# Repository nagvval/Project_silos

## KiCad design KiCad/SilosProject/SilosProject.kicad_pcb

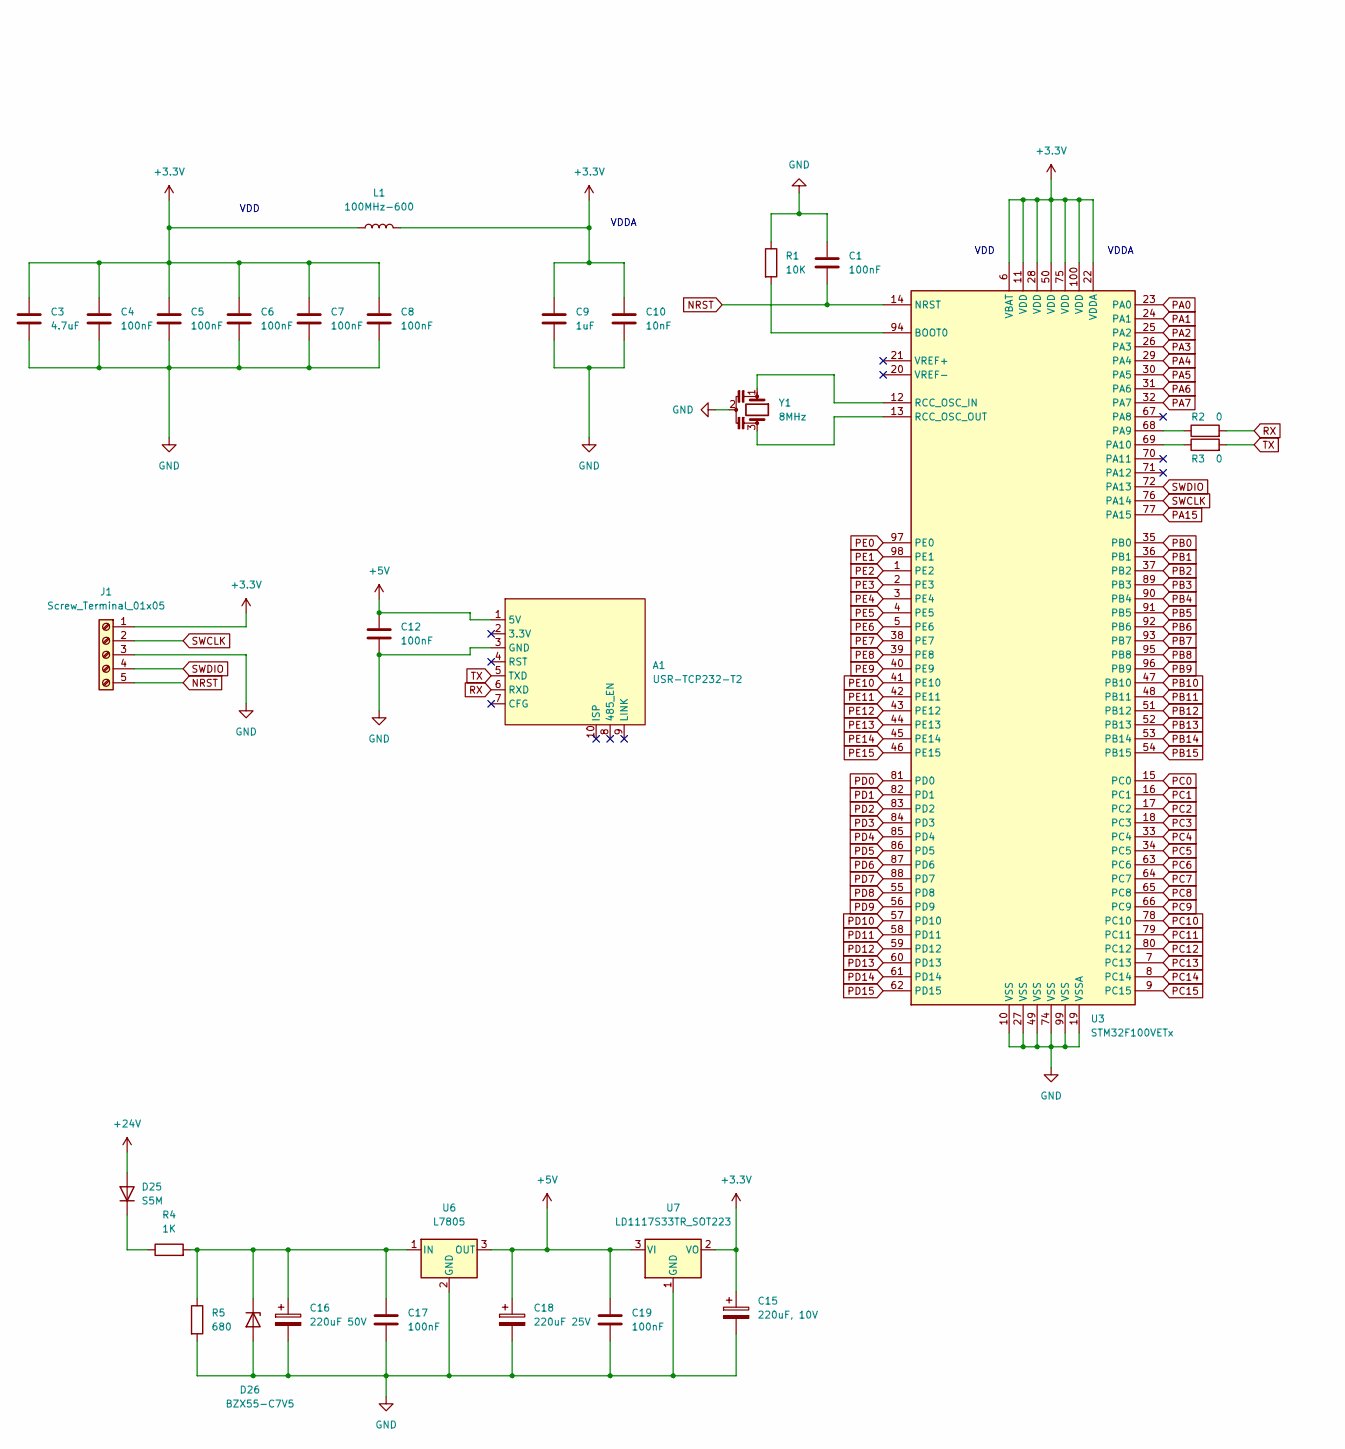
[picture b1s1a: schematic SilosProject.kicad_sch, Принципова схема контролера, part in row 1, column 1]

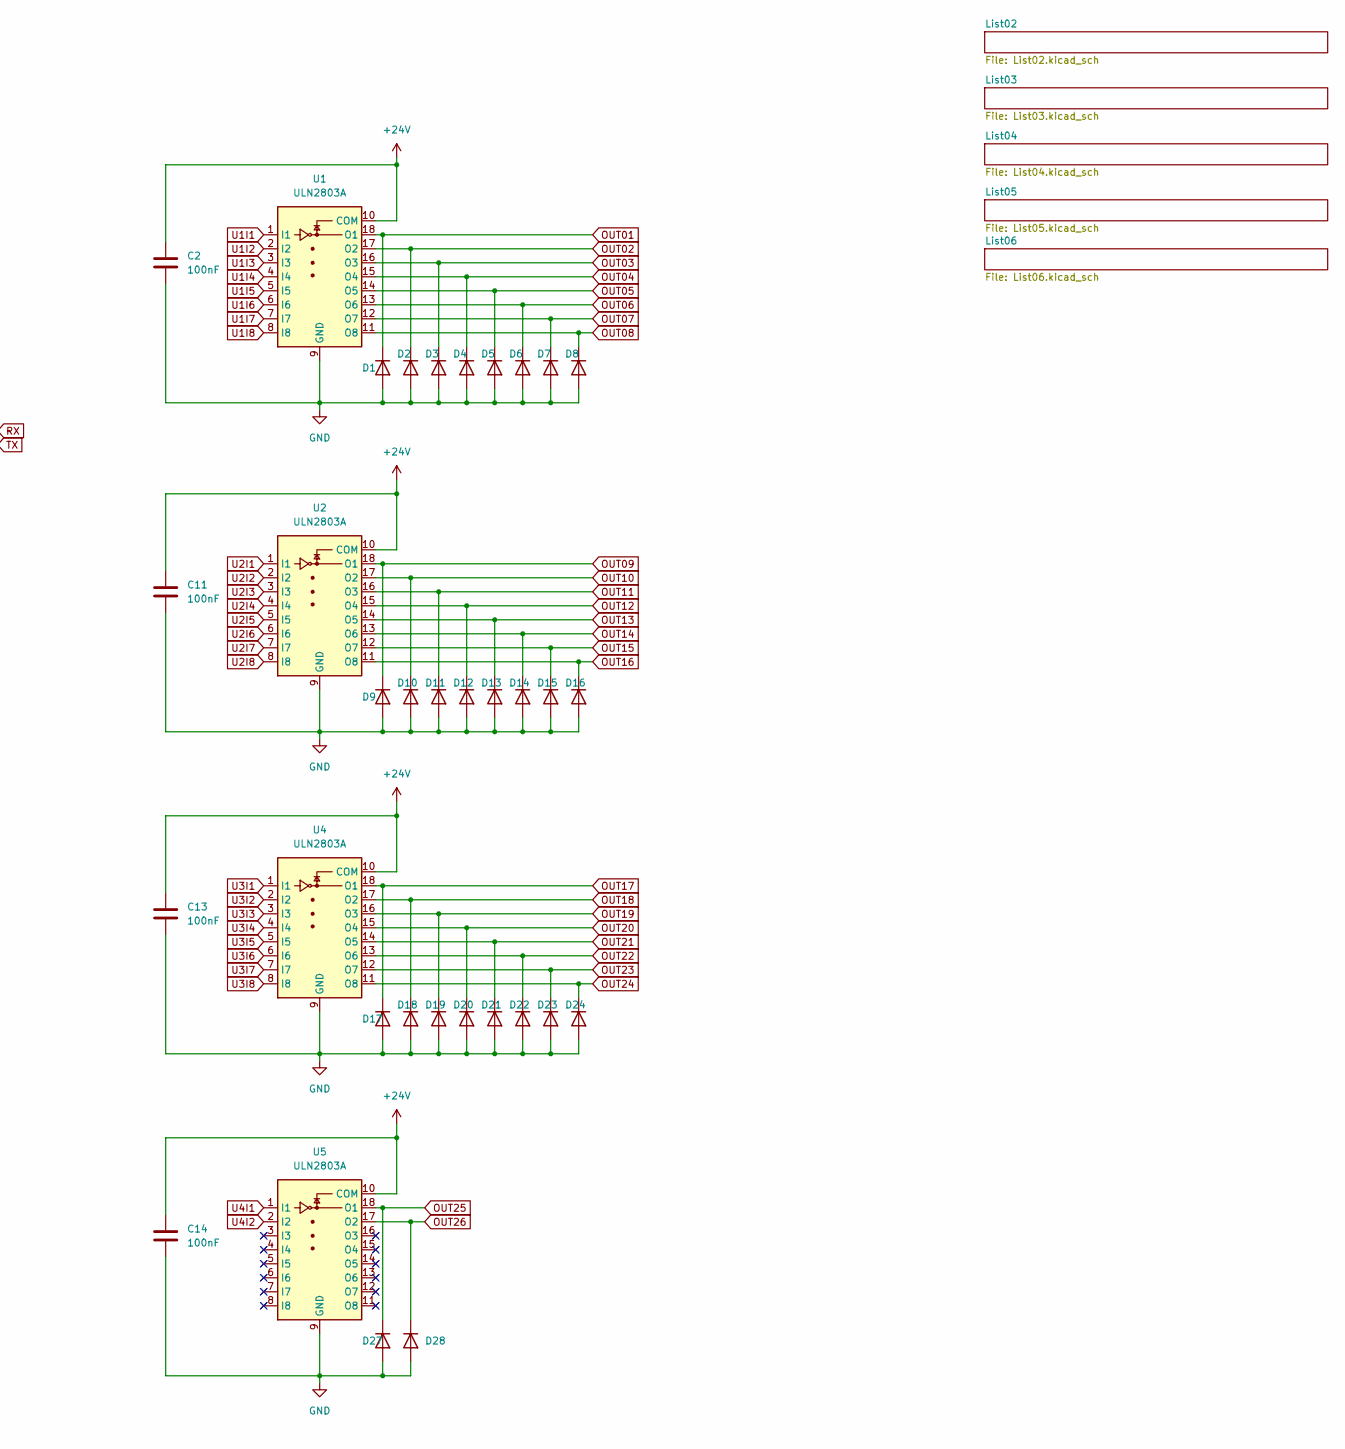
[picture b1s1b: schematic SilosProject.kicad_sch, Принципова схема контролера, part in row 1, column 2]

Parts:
A1: USR-TCP232-T2; USR-TCP232-T2_MODUL
C1, C2, C4, C5, C6, C7, C8, C11, C12, C13, C14, C17, C19: 100nF; C_0805_2012Metric
C3: 4.7uF; C_0805_2012Metric
C9: 1uF; C_0805_2012Metric
C10: 10nF; C_0805_2012Metric
C15: 220uF, 10V; C_Radial_D6.3mm_H11.0mm_P2.50mm
C16: 220uF 50V; C_Radial_D10.0mm_H12.5mm_P5.00mm
C18: 220uF 25V; C_Radial_D6.3mm_H11.0mm_P2.50mm
D1, D2, D3, D4, D5, D6, D7, D8, D9, D10, D11, D12, D13, D14, D15, D16, D17, D18, D19, D20, D21, D22, D23, D24, D27, D28: 1N4007; D_DO-41_SOD81_P10.16mm_Horizontal
D25: S5M; D_SMC
D26: BZX55-C7V5; D_SOD-123
J1: Screw_Terminal_01x05; PinHeader_1x05_P2.54mm_Vertical
L1: 100MHz-600; L_0805_2012Metric_Pad1.05x1.20mm_HandSolder
R1: 10K; C_0805_2012Metric
R2, R3: 0; R_0805_2012Metric
R4: 1K; R_2512_6332Metric
R5: 680; R_2512_6332Metric
U1, U2, U4, U5: ULN2803A; SOIC-18W_7.5x11.6mm_P1.27mm
U3: STM32F100VETx; LQFP-100_14x14mm_P0.5mm
U6: L7805; TO-220-3_Vertical
U7: LD1117S33TR_SOT223; SOT-223-3_TabPin2
Y1: 8MHz; Resonator_SMD_Murata_CSTxExxV-3Pin_3.0x1.1mm

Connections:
+3.3V: C3.1, C4.1, C5.1, C6.1, C7.1, C8.1, C9.1, C10.1, C15.1, J1.1, L1.1, L1.2, U3.6 (VBAT), U3.11 (VDD), U3.22 (VDDA), U3.28 (VDD), U3.50 (VDD), U3.75 (VDD), U3.100 (VDD), U7.2 (VO); also elsewhere on the board
+5V: A1.1 (5V), C12.1, C18.1, C19.1, U6.3 (OUT), U7.3 (VI); also elsewhere on the board
+24V: C2.1, C11.1, C13.1, C14.1, D25.2 (A), U1.10 (COM), U2.10 (COM), U4.10 (COM), U5.10 (COM); also elsewhere on the board
GND: A1.3 (GND), C1.2, C2.2, C3.2, C4.2, C5.2, C6.2, C7.2, C8.2, C9.2, C10.2, C11.2, C12.2, C13.2, C14.2, C15.2, C16.2, C17.2, C18.2, C19.2, D1.2 (A), D2.2 (A), D3.2 (A), D4.2 (A), D5.2 (A), D6.2 (A), D7.2 (A), D8.2 (A), D9.2 (A), D10.2 (A), D11.2 (A), D12.2 (A), D13.2 (A), D14.2 (A), D15.2 (A), D16.2 (A), D17.2 (A), D18.2 (A), D19.2 (A), D20.2 (A), D21.2 (A), D22.2 (A), D23.2 (A), D24.2 (A), D26.2 (A), D27.2 (A), D28.2 (A), J1.3, R1.1, R5.2, U1.9 (GND), U2.9 (GND), U3.10 (VSS), U3.19 (VSSA), U3.27 (VSS), U3.49 (VSS), U3.74 (VSS), U3.99 (VSS), U4.9 (GND), U5.9 (GND), U6.2 (GND), U7.1 (GND), Y1.2; also elsewhere on the board
NRST: C1.1, J1.5, U3.14 (NRST)
unnamed: C16.1, C17.1, D26.1 (K), R4.2, R5.1, U6.1 (IN)
unnamed: D25.1 (K), R4.1
unnamed: R1.2, U3.94 (BOOT0)
unnamed: R2.1, U3.68 (PA9)
unnamed: R3.1, U3.69 (PA10)
unnamed: U3.12 (RCC_OSC_IN), Y1.1
unnamed: U3.13 (RCC_OSC_OUT), Y1.3
OUT01: D1.1 (K), U1.18 (O1); also elsewhere on the board
OUT02: D2.1 (K), U1.17 (O2); also elsewhere on the board
OUT03: D3.1 (K), U1.16 (O3); also elsewhere on the board
OUT04: D4.1 (K), U1.15 (O4); also elsewhere on the board
OUT05: D5.1 (K), U1.14 (O5); also elsewhere on the board
OUT06: D6.1 (K), U1.13 (O6); also elsewhere on the board
OUT07: D7.1 (K), U1.12 (O7); also elsewhere on the board
OUT08: D8.1 (K), U1.11 (O8); also elsewhere on the board
OUT09: D9.1 (K), U2.18 (O1); also elsewhere on the board
OUT10: D10.1 (K), U2.17 (O2); also elsewhere on the board
OUT11: D11.1 (K), U2.16 (O3); also elsewhere on the board
OUT12: D12.1 (K), U2.15 (O4); also elsewhere on the board
OUT13: D13.1 (K), U2.14 (O5); also elsewhere on the board
OUT14: D14.1 (K), U2.13 (O6); also elsewhere on the board
OUT15: D15.1 (K), U2.12 (O7); also elsewhere on the board
OUT16: D16.1 (K), U2.11 (O8); also elsewhere on the board
OUT17: D17.1 (K), U4.18 (O1); also elsewhere on the board
OUT18: D18.1 (K), U4.17 (O2); also elsewhere on the board
OUT19: D19.1 (K), U4.16 (O3); also elsewhere on the board
OUT20: D20.1 (K), U4.15 (O4); also elsewhere on the board
OUT21: D21.1 (K), U4.14 (O5); also elsewhere on the board
OUT22: D22.1 (K), U4.13 (O6); also elsewhere on the board
OUT23: D23.1 (K), U4.12 (O7); also elsewhere on the board
OUT24: D24.1 (K), U4.11 (O8); also elsewhere on the board
OUT25: D27.1 (K), U5.18 (O1); also elsewhere on the board
OUT26: D28.1 (K), U5.17 (O2); also elsewhere on the board
PA0: U3.23 (PA0); also elsewhere on the board
PA1: U3.24 (PA1); also elsewhere on the board
PA2: U3.25 (PA2); also elsewhere on the board
PA3: U3.26 (PA3); also elsewhere on the board
PA4: U3.29 (PA4); also elsewhere on the board
PA5: U3.30 (PA5); also elsewhere on the board
PA6: U3.31 (PA6); also elsewhere on the board
PA7: U3.32 (PA7); also elsewhere on the board
PA15: U3.77 (PA15); also elsewhere on the board
PB0: U3.35 (PB0); also elsewhere on the board
PB1: U3.36 (PB1); also elsewhere on the board
PB2: U3.37 (PB2); also elsewhere on the board
PB3: U3.89 (PB3); also elsewhere on the board
PB4: U3.90 (PB4); also elsewhere on the board
PB5: U3.91 (PB5); also elsewhere on the board
PB6: U3.92 (PB6); also elsewhere on the board
PB7: U3.93 (PB7); also elsewhere on the board
PB8: U3.95 (PB8); also elsewhere on the board
PB9: U3.96 (PB9); also elsewhere on the board
PB10: U3.47 (PB10); also elsewhere on the board
PB11: U3.48 (PB11); also elsewhere on the board
PB12: U3.51 (PB12); also elsewhere on the board
PB13: U3.52 (PB13); also elsewhere on the board
PB14: U3.53 (PB14); also elsewhere on the board
PB15: U3.54 (PB15); also elsewhere on the board
PC0: U3.15 (PC0); also elsewhere on the board
PC1: U3.16 (PC1); also elsewhere on the board
PC2: U3.17 (PC2); also elsewhere on the board
PC3: U3.18 (PC3); also elsewhere on the board
PC4: U3.33 (PC4); also elsewhere on the board
PC5: U3.34 (PC5); also elsewhere on the board
PC6: U3.63 (PC6); also elsewhere on the board
PC7: U3.64 (PC7); also elsewhere on the board
PC8: U3.65 (PC8); also elsewhere on the board
PC9: U3.66 (PC9); also elsewhere on the board
PC10: U3.78 (PC10); also elsewhere on the board
PC11: U3.79 (PC11); also elsewhere on the board
PC12: U3.80 (PC12); also elsewhere on the board
PC13: U3.7 (PC13); also elsewhere on the board
PC14: U3.8 (PC14); also elsewhere on the board
PC15: U3.9 (PC15); also elsewhere on the board
PD0: U3.81 (PD0); also elsewhere on the board
PD1: U3.82 (PD1); also elsewhere on the board
PD2: U3.83 (PD2); also elsewhere on the board
PD3: U3.84 (PD3); also elsewhere on the board
PD4: U3.85 (PD4); also elsewhere on the board
PD5: U3.86 (PD5); also elsewhere on the board
PD6: U3.87 (PD6); also elsewhere on the board
PD7: U3.88 (PD7); also elsewhere on the board
PD8: U3.55 (PD8); also elsewhere on the board
PD9: U3.56 (PD9); also elsewhere on the board
PD10: U3.57 (PD10); also elsewhere on the board
PD11: U3.58 (PD11); also elsewhere on the board
PD12: U3.59 (PD12); also elsewhere on the board
PD13: U3.60 (PD13); also elsewhere on the board
PD14: U3.61 (PD14); also elsewhere on the board
PD15: U3.62 (PD15); also elsewhere on the board
PE0: U3.97 (PE0); also elsewhere on the board
PE1: U3.98 (PE1); also elsewhere on the board
PE2: U3.1 (PE2); also elsewhere on the board
PE3: U3.2 (PE3); also elsewhere on the board
PE4: U3.3 (PE4); also elsewhere on the board
PE5: U3.4 (PE5); also elsewhere on the board
PE6: U3.5 (PE6); also elsewhere on the board
PE7: U3.38 (PE7); also elsewhere on the board
PE8: U3.39 (PE8); also elsewhere on the board
PE9: U3.40 (PE9); also elsewhere on the board
PE10: U3.41 (PE10); also elsewhere on the board
PE11: U3.42 (PE11); also elsewhere on the board
PE12: U3.43 (PE12); also elsewhere on the board
PE13: U3.44 (PE13); also elsewhere on the board
PE14: U3.45 (PE14); also elsewhere on the board
PE15: U3.46 (PE15); also elsewhere on the board
RX: A1.6 (RXD), R2.2
SWCLK: J1.2, U3.76 (PA14)
SWDIO: J1.4, U3.72 (PA13)
TX: A1.5 (TXD), R3.2
U1I1: U1.1 (I1); also elsewhere on the board
U1I2: U1.2 (I2); also elsewhere on the board
U1I3: U1.3 (I3); also elsewhere on the board
U1I4: U1.4 (I4); also elsewhere on the board
U1I5: U1.5 (I5); also elsewhere on the board
U1I6: U1.6 (I6); also elsewhere on the board
U1I7: U1.7 (I7); also elsewhere on the board
U1I8: U1.8 (I8); also elsewhere on the board
U2I1: U2.1 (I1); also elsewhere on the board
U2I2: U2.2 (I2); also elsewhere on the board
U2I3: U2.3 (I3); also elsewhere on the board
U2I4: U2.4 (I4); also elsewhere on the board
U2I5: U2.5 (I5); also elsewhere on the board
U2I6: U2.6 (I6); also elsewhere on the board
U2I7: U2.7 (I7); also elsewhere on the board
U2I8: U2.8 (I8); also elsewhere on the board
U3I1: U4.1 (I1); also elsewhere on the board
U3I2: U4.2 (I2); also elsewhere on the board
U3I3: U4.3 (I3); also elsewhere on the board
U3I4: U4.4 (I4); also elsewhere on the board
U3I5: U4.5 (I5); also elsewhere on the board
U3I6: U4.6 (I6); also elsewhere on the board
U3I7: U4.7 (I7); also elsewhere on the board
U3I8: U4.8 (I8); also elsewhere on the board
U4I1: U5.1 (I1); also elsewhere on the board
U4I2: U5.2 (I2); also elsewhere on the board

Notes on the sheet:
VDD
VDDA

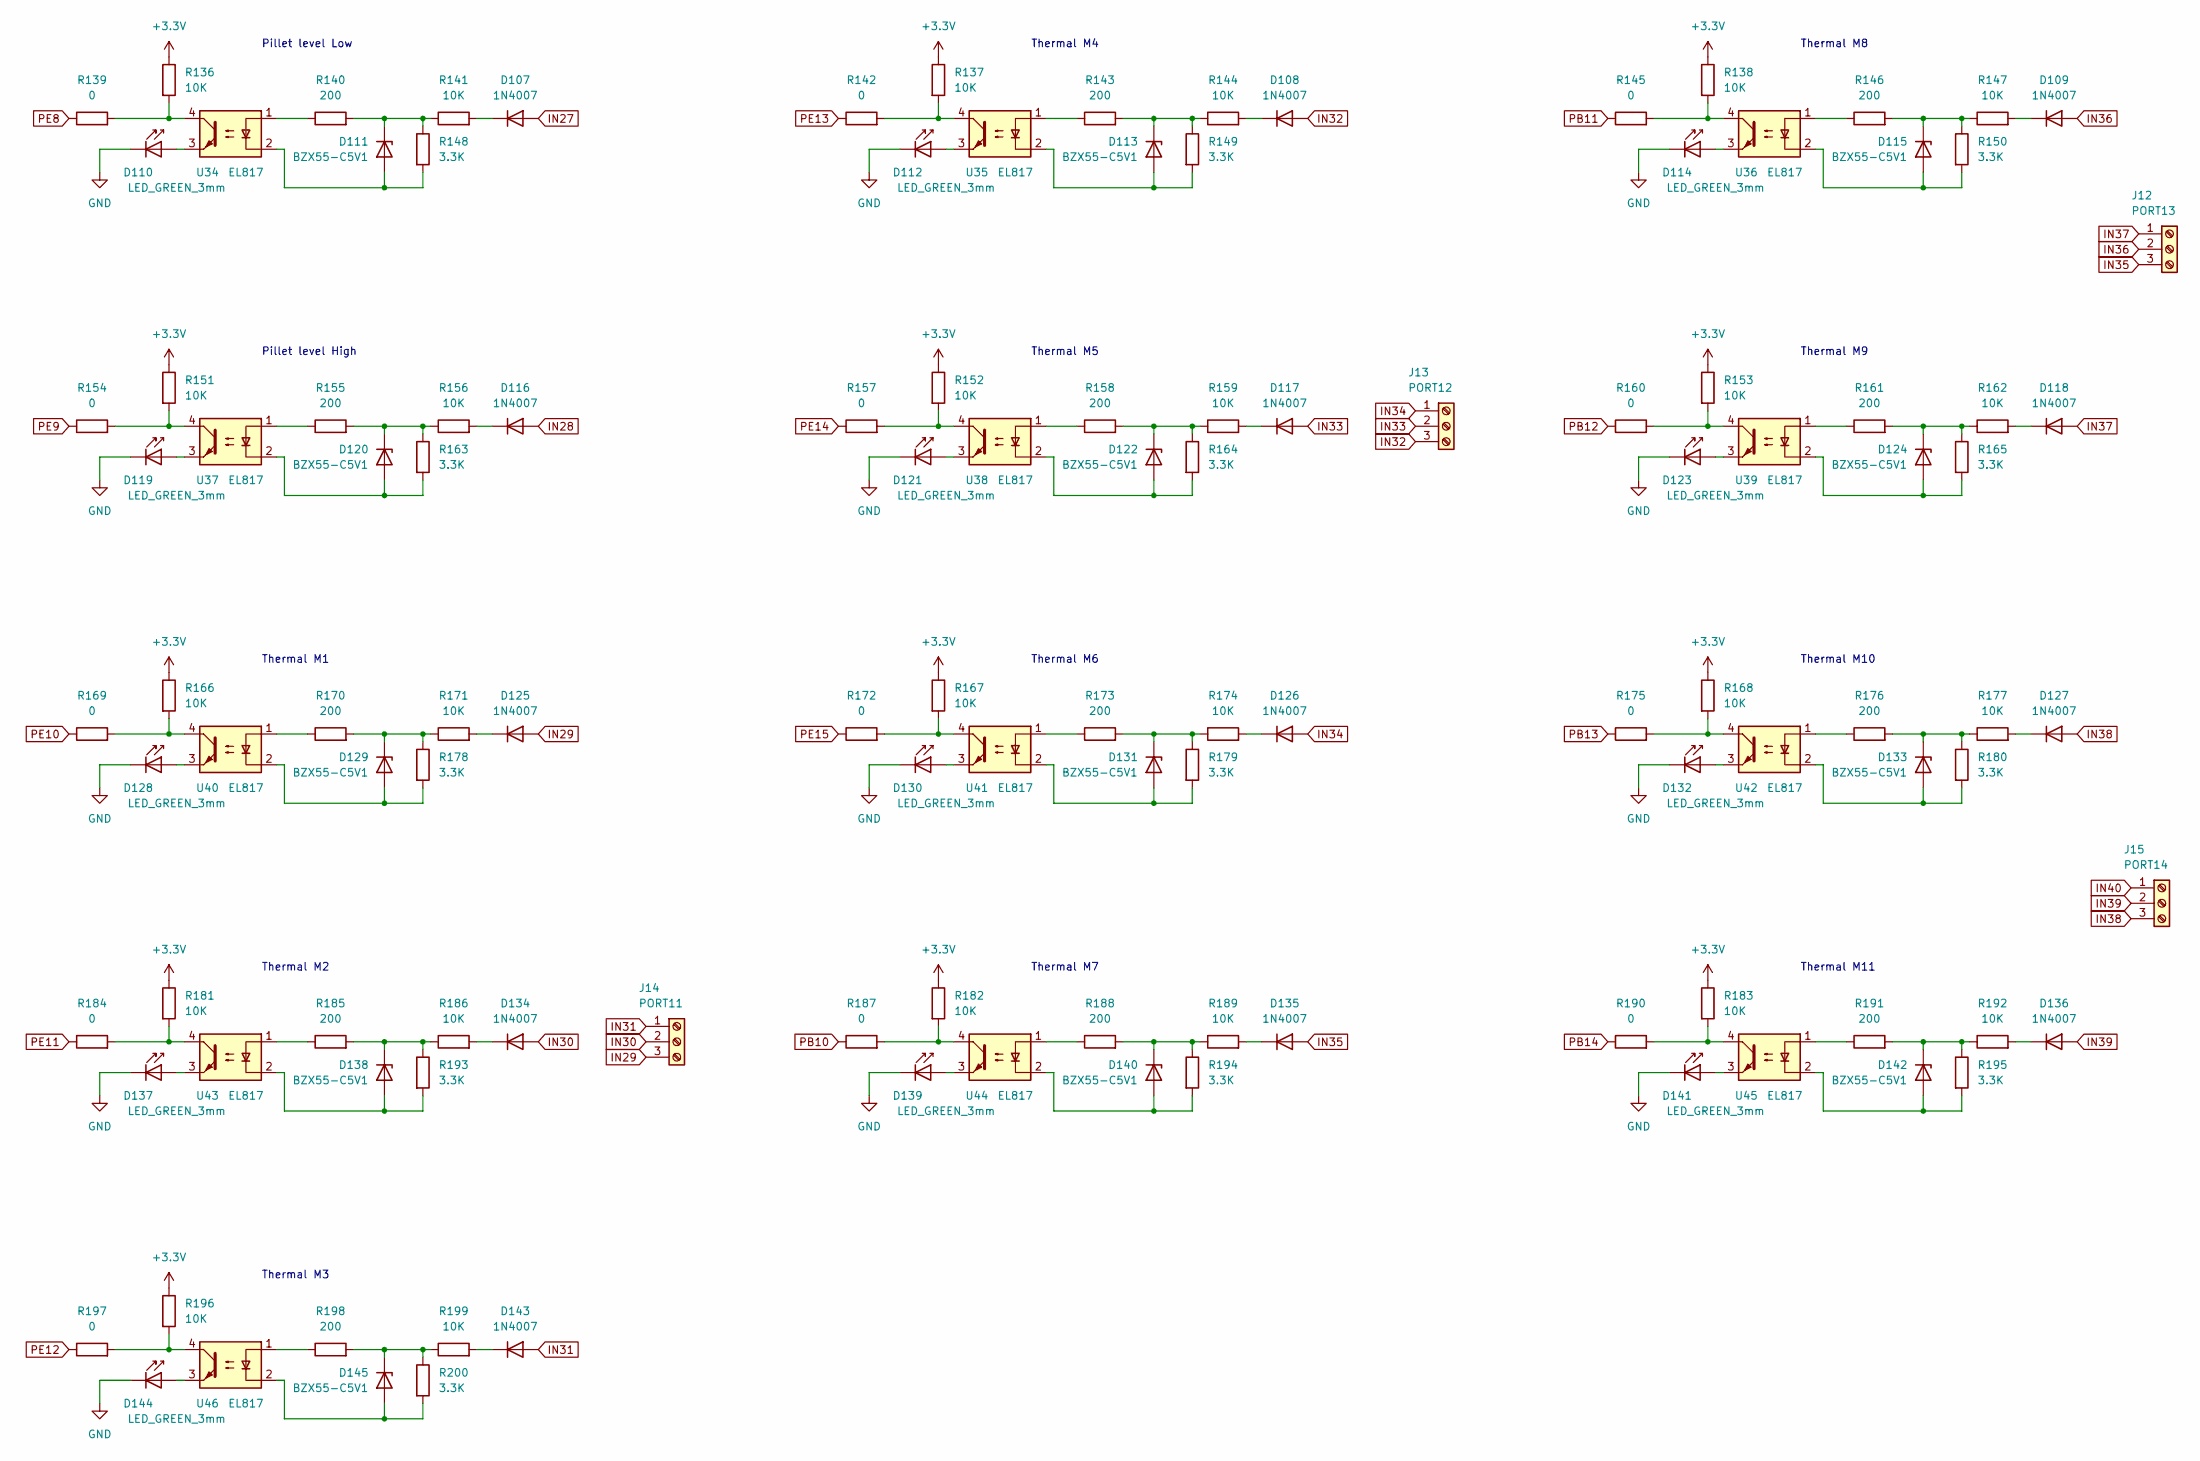
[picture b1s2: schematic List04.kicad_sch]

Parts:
D107, D108, D109, D116, D117, D118, D125, D126, D127, D134, D135, D136, D143: 1N4007; D_DO-41_SOD81_P10.16mm_Horizontal
D110, D112, D114, D119, D121, D123, D128, D130, D132, D137, D139, D141, D144: LED_GREEN_3mm; LED_D3.0mm
D111, D113, D115, D120, D122, D124, D129, D131, D133, D138, D140, D142, D145: BZX55-C5V1; D_DO-35_SOD27_P2.54mm_Vertical_AnodeUp
J12: PORT13; DG306-5.0-03P-12-00A
J13: PORT12; DG306-5.0-03P-12-00A
J14: PORT11; DG306-5.0-03P-12-00A
J15: PORT14; DG306-5.0-03P-12-00A
R136, R137, R138, R151, R152, R153, R166, R167, R168, R181, R182, R183, R196: 10K; R_0805_2012Metric
R139, R142, R145, R154, R157, R160, R169, R172, R175, R184, R187, R190, R197: 0; R_0805_2012Metric
R140, R143, R146, R155, R158, R161, R170, R173, R176, R185, R188, R191, R198: 200; R_0805_2012Metric
R141, R144, R147, R156, R159, R162, R171, R174, R177, R186, R189, R192, R199: 10K; R_2512_6332Metric
R148, R149, R150, R163, R164, R165, R178, R179, R180, R193, R194, R195, R200: 3.3K; R_1206_3216Metric
U34, U35, U36, U37, U38, U39, U40, U41, U42, U43, U44, U45, U46: EL817; DIP-4_W7.62mm

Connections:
+3.3V: R136.1, R137.1, R138.1, R151.1, R152.1, R153.1, R166.1, R167.1, R168.1, R181.1, R182.1, R183.1, R196.1; also elsewhere on the board
GND: D110.1 (K), D112.1 (K), D114.1 (K), D119.1 (K), D121.1 (K), D123.1 (K), D128.1 (K), D130.1 (K), D132.1 (K), D137.1 (K), D139.1 (K), D141.1 (K), D144.1 (K); also elsewhere on the board
IN27: D107.2 (A); also elsewhere on the board
IN28: D116.2 (A); also elsewhere on the board
IN29: D125.2 (A), J14.3
IN30: D134.2 (A), J14.2
IN31: D143.2 (A), J14.1
IN32: D108.2 (A), J13.3
IN33: D117.2 (A), J13.2
IN34: D126.2 (A), J13.1
IN35: D135.2 (A), J12.3
IN36: D109.2 (A), J12.2
IN37: D118.2 (A), J12.1
IN38: D127.2 (A), J15.3
IN39: D136.2 (A), J15.2
IN40: J15.1; also elsewhere on the board
unnamed: D107.1 (K), R141.2
unnamed: D108.1 (K), R144.2
unnamed: D109.1 (K), R147.2
unnamed: D110.2 (A), U34.3
unnamed: D111.1 (K), R140.2, R141.1, R148.1
unnamed: D111.2 (A), R148.2, U34.2
unnamed: D112.2 (A), U35.3
unnamed: D113.1 (K), R143.2, R144.1, R149.1
unnamed: D113.2 (A), R149.2, U35.2
unnamed: D114.2 (A), U36.3
unnamed: D115.1 (K), R146.2, R147.1, R150.1
unnamed: D115.2 (A), R150.2, U36.2
unnamed: D116.1 (K), R156.2
unnamed: D117.1 (K), R159.2
unnamed: D118.1 (K), R162.2
unnamed: D119.2 (A), U37.3
unnamed: D120.1 (K), R155.2, R156.1, R163.1
unnamed: D120.2 (A), R163.2, U37.2
unnamed: D121.2 (A), U38.3
unnamed: D122.1 (K), R158.2, R159.1, R164.1
unnamed: D122.2 (A), R164.2, U38.2
unnamed: D123.2 (A), U39.3
unnamed: D124.1 (K), R161.2, R162.1, R165.1
unnamed: D124.2 (A), R165.2, U39.2
unnamed: D125.1 (K), R171.2
unnamed: D126.1 (K), R174.2
unnamed: D127.1 (K), R177.2
unnamed: D128.2 (A), U40.3
unnamed: D129.1 (K), R170.2, R171.1, R178.1
unnamed: D129.2 (A), R178.2, U40.2
unnamed: D130.2 (A), U41.3
unnamed: D131.1 (K), R173.2, R174.1, R179.1
unnamed: D131.2 (A), R179.2, U41.2
unnamed: D132.2 (A), U42.3
unnamed: D133.1 (K), R176.2, R177.1, R180.1
unnamed: D133.2 (A), R180.2, U42.2
unnamed: D134.1 (K), R186.2
unnamed: D135.1 (K), R189.2
unnamed: D136.1 (K), R192.2
unnamed: D137.2 (A), U43.3
unnamed: D138.1 (K), R185.2, R186.1, R193.1
unnamed: D138.2 (A), R193.2, U43.2
unnamed: D139.2 (A), U44.3
unnamed: D140.1 (K), R188.2, R189.1, R194.1
unnamed: D140.2 (A), R194.2, U44.2
unnamed: D141.2 (A), U45.3
unnamed: D142.1 (K), R191.2, R192.1, R195.1
unnamed: D142.2 (A), R195.2, U45.2
unnamed: D143.1 (K), R199.2
unnamed: D144.2 (A), U46.3
unnamed: D145.1 (K), R198.2, R199.1, R200.1
unnamed: D145.2 (A), R200.2, U46.2
unnamed: R136.2, R139.2, U34.4
unnamed: R137.2, R142.2, U35.4
unnamed: R138.2, R145.2, U36.4
unnamed: R140.1, U34.1
unnamed: R143.1, U35.1
unnamed: R146.1, U36.1
unnamed: R151.2, R154.2, U37.4
unnamed: R152.2, R157.2, U38.4
unnamed: R153.2, R160.2, U39.4
unnamed: R155.1, U37.1
unnamed: R158.1, U38.1
unnamed: R161.1, U39.1
unnamed: R166.2, R169.2, U40.4
unnamed: R167.2, R172.2, U41.4
unnamed: R168.2, R175.2, U42.4
unnamed: R170.1, U40.1
unnamed: R173.1, U41.1
unnamed: R176.1, U42.1
unnamed: R181.2, R184.2, U43.4
unnamed: R182.2, R187.2, U44.4
unnamed: R183.2, R190.2, U45.4
unnamed: R185.1, U43.1
unnamed: R188.1, U44.1
unnamed: R191.1, U45.1
unnamed: R196.2, R197.2, U46.4
unnamed: R198.1, U46.1
PB10: R187.1; also elsewhere on the board
PB11: R145.1; also elsewhere on the board
PB12: R160.1; also elsewhere on the board
PB13: R175.1; also elsewhere on the board
PB14: R190.1; also elsewhere on the board
PE8: R139.1; also elsewhere on the board
PE9: R154.1; also elsewhere on the board
PE10: R169.1; also elsewhere on the board
PE11: R184.1; also elsewhere on the board
PE12: R197.1; also elsewhere on the board
PE13: R142.1; also elsewhere on the board
PE14: R157.1; also elsewhere on the board
PE15: R172.1; also elsewhere on the board

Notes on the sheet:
Pillet level Low
Thermal M6
Pillet level High
Thermal M1
Thermal M3
Thermal M8
Thermal M4
Thermal M5
Thermal M10
Thermal M7
Thermal M11
Thermal M2
Thermal M9

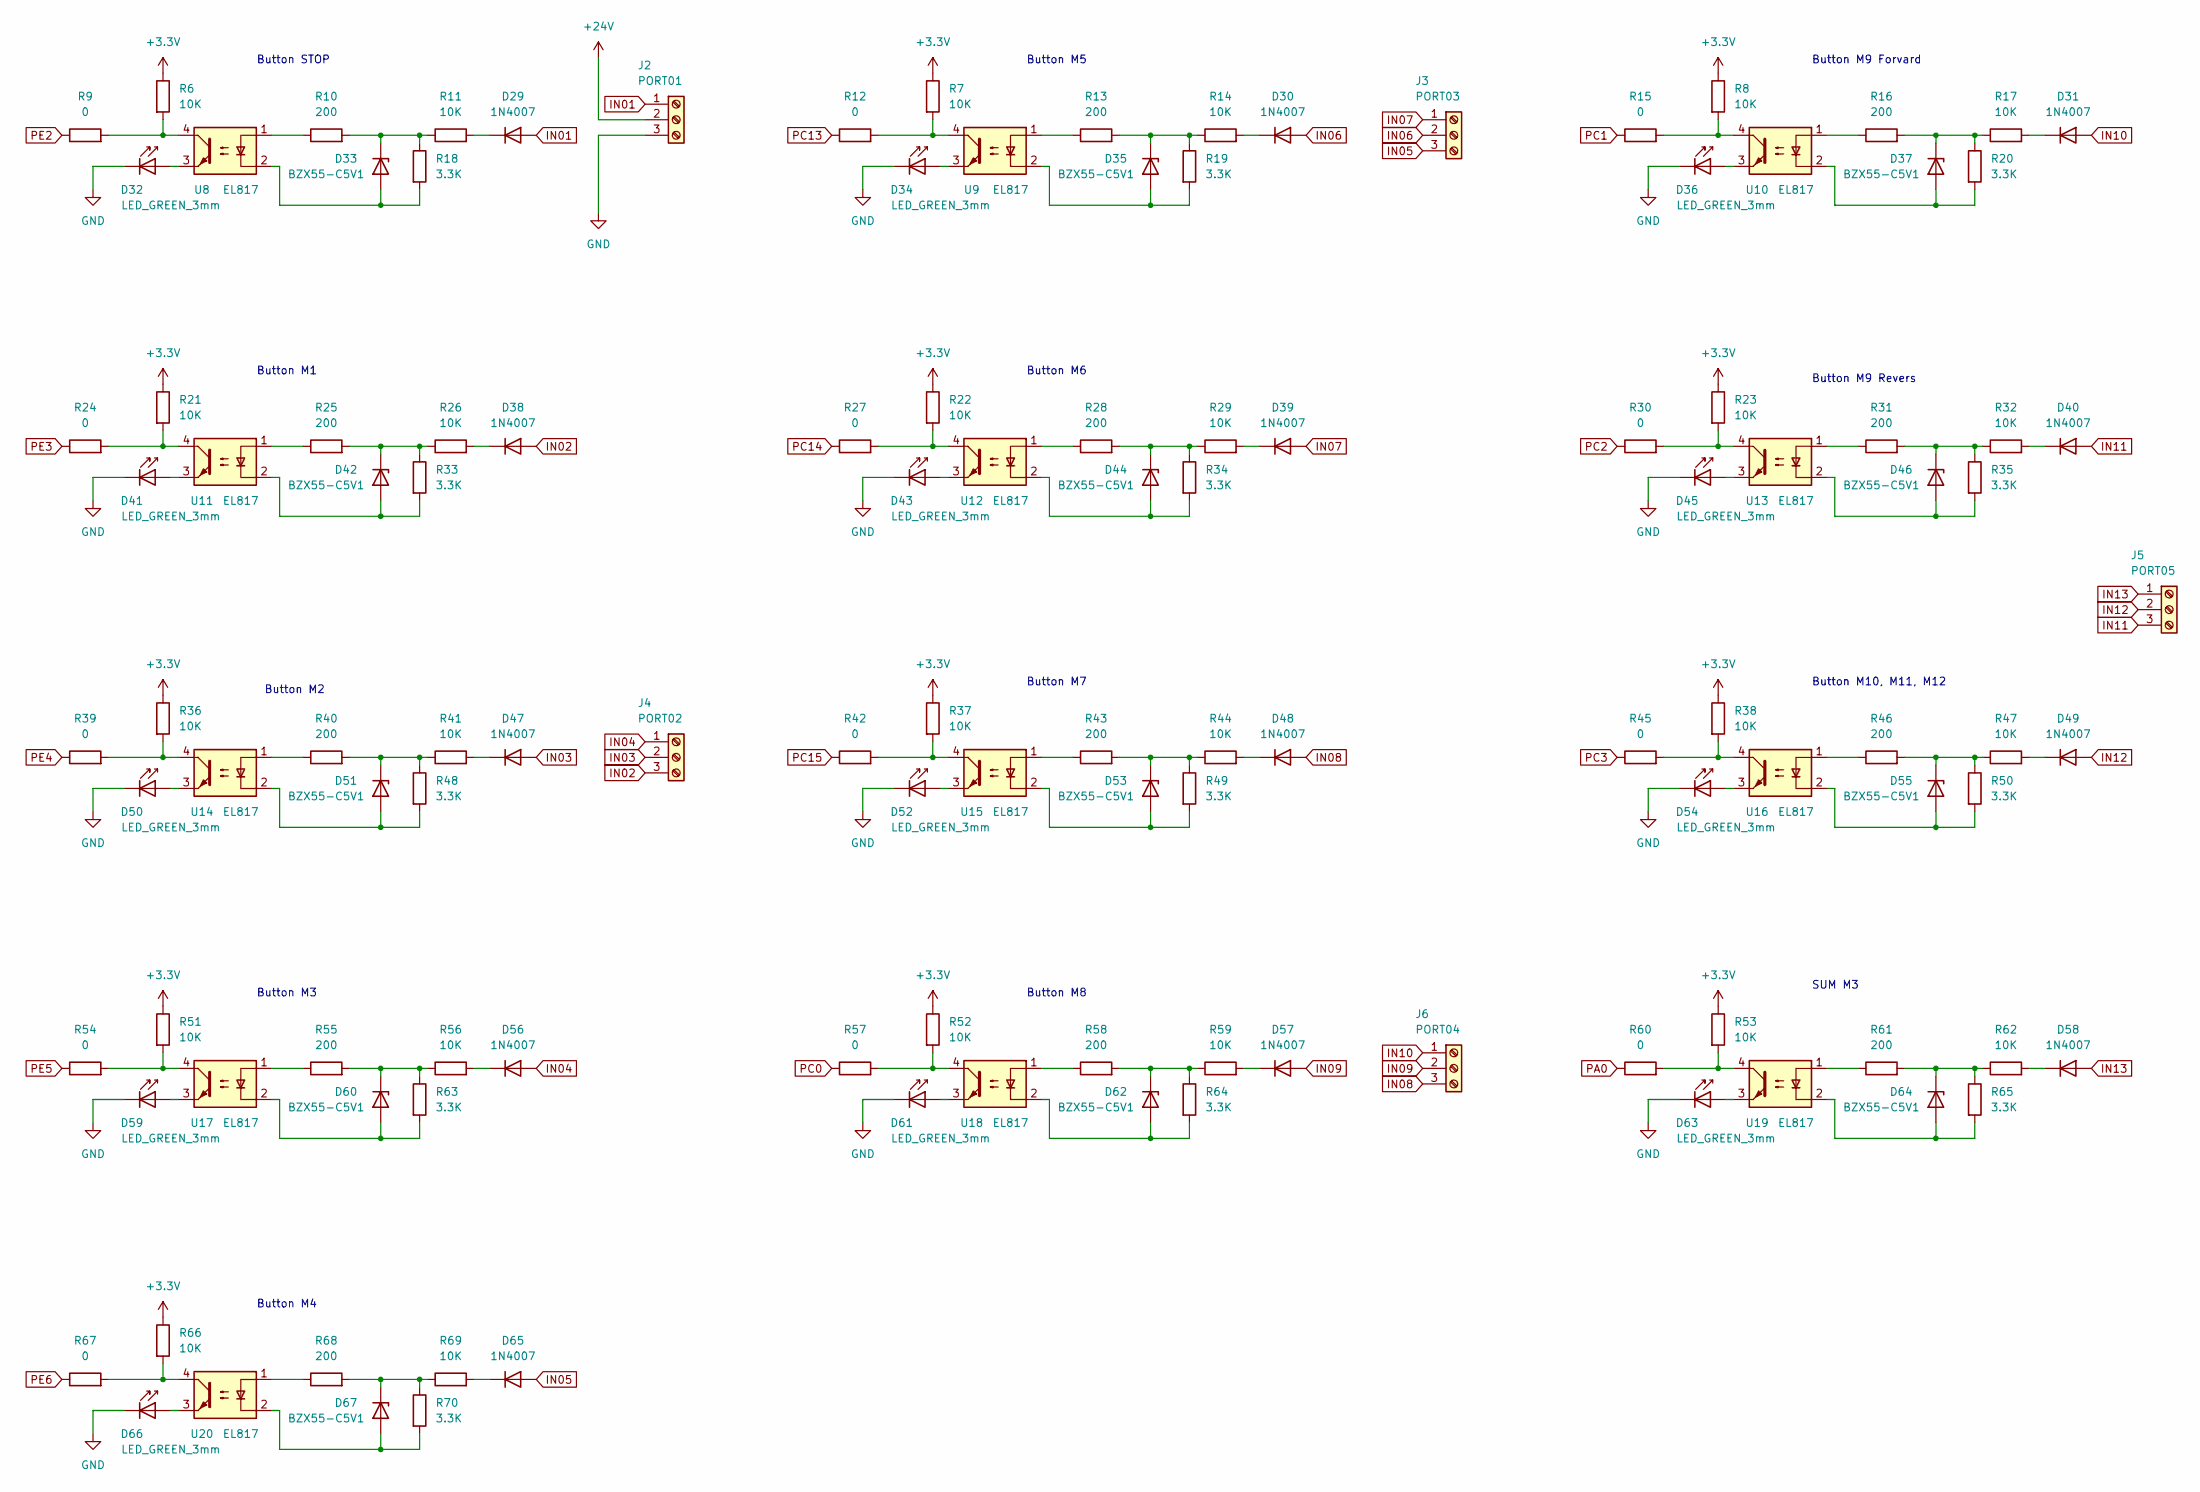
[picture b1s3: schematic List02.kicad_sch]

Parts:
D29, D30, D31, D38, D39, D40, D47, D48, D49, D56, D57, D58, D65: 1N4007; D_DO-41_SOD81_P10.16mm_Horizontal
D32, D34, D36, D41, D43, D45, D50, D52, D54, D59, D61, D63, D66: LED_GREEN_3mm; LED_D3.0mm
D33, D35, D37, D42, D44, D46, D51, D53, D55, D60, D62, D64, D67: BZX55-C5V1; D_DO-35_SOD27_P2.54mm_Vertical_AnodeUp
J2: PORT01; DG306-5.0-03P-12-00A
J3: PORT03; DG306-5.0-03P-12-00A
J4: PORT02; DG306-5.0-03P-12-00A
J5: PORT05; DG306-5.0-03P-12-00A
J6: PORT04; DG306-5.0-03P-12-00A
R6, R7, R8, R21, R22, R23, R36, R37, R38, R51, R52, R53, R66: 10K; R_0805_2012Metric
R9, R12, R15, R24, R27, R30, R39, R42, R45, R54, R57, R60, R67: 0; R_0805_2012Metric
R10, R13, R16, R25, R28, R31, R40, R43, R46, R55, R58, R61, R68: 200; R_0805_2012Metric
R11, R14, R17, R26, R29, R32, R41, R44, R47, R56, R59, R62, R69: 10K; R_2512_6332Metric
R18, R19, R20, R33, R34, R35, R48, R49, R50, R63, R64, R65, R70: 3.3K; R_1206_3216Metric
U8, U9, U10, U11, U12, U13, U14, U15, U16, U17, U18, U19, U20: EL817; DIP-4_W7.62mm

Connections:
+3.3V: R6.1, R7.1, R8.1, R21.1, R22.1, R23.1, R36.1, R37.1, R38.1, R51.1, R52.1, R53.1, R66.1; also elsewhere on the board
+24V: J2.2; also elsewhere on the board
GND: D32.1 (K), D34.1 (K), D36.1 (K), D41.1 (K), D43.1 (K), D45.1 (K), D50.1 (K), D52.1 (K), D54.1 (K), D59.1 (K), D61.1 (K), D63.1 (K), D66.1 (K), J2.3; also elsewhere on the board
IN01: D29.2 (A), J2.1
IN02: D38.2 (A), J4.3
IN03: D47.2 (A), J4.2
IN04: D56.2 (A), J4.1
IN05: D65.2 (A), J3.3
IN06: D30.2 (A), J3.2
IN07: D39.2 (A), J3.1
IN08: D48.2 (A), J6.3
IN09: D57.2 (A), J6.2
IN10: D31.2 (A), J6.1
IN11: D40.2 (A), J5.3
IN12: D49.2 (A), J5.2
IN13: D58.2 (A), J5.1
unnamed: D29.1 (K), R11.2
unnamed: D30.1 (K), R14.2
unnamed: D31.1 (K), R17.2
unnamed: D32.2 (A), U8.3
unnamed: D33.1 (K), R10.2, R11.1, R18.1
unnamed: D33.2 (A), R18.2, U8.2
unnamed: D34.2 (A), U9.3
unnamed: D35.1 (K), R13.2, R14.1, R19.1
unnamed: D35.2 (A), R19.2, U9.2
unnamed: D36.2 (A), U10.3
unnamed: D37.1 (K), R16.2, R17.1, R20.1
unnamed: D37.2 (A), R20.2, U10.2
unnamed: D38.1 (K), R26.2
unnamed: D39.1 (K), R29.2
unnamed: D40.1 (K), R32.2
unnamed: D41.2 (A), U11.3
unnamed: D42.1 (K), R25.2, R26.1, R33.1
unnamed: D42.2 (A), R33.2, U11.2
unnamed: D43.2 (A), U12.3
unnamed: D44.1 (K), R28.2, R29.1, R34.1
unnamed: D44.2 (A), R34.2, U12.2
unnamed: D45.2 (A), U13.3
unnamed: D46.1 (K), R31.2, R32.1, R35.1
unnamed: D46.2 (A), R35.2, U13.2
unnamed: D47.1 (K), R41.2
unnamed: D48.1 (K), R44.2
unnamed: D49.1 (K), R47.2
unnamed: D50.2 (A), U14.3
unnamed: D51.1 (K), R40.2, R41.1, R48.1
unnamed: D51.2 (A), R48.2, U14.2
unnamed: D52.2 (A), U15.3
unnamed: D53.1 (K), R43.2, R44.1, R49.1
unnamed: D53.2 (A), R49.2, U15.2
unnamed: D54.2 (A), U16.3
unnamed: D55.1 (K), R46.2, R47.1, R50.1
unnamed: D55.2 (A), R50.2, U16.2
unnamed: D56.1 (K), R56.2
unnamed: D57.1 (K), R59.2
unnamed: D58.1 (K), R62.2
unnamed: D59.2 (A), U17.3
unnamed: D60.1 (K), R55.2, R56.1, R63.1
unnamed: D60.2 (A), R63.2, U17.2
unnamed: D61.2 (A), U18.3
unnamed: D62.1 (K), R58.2, R59.1, R64.1
unnamed: D62.2 (A), R64.2, U18.2
unnamed: D63.2 (A), U19.3
unnamed: D64.1 (K), R61.2, R62.1, R65.1
unnamed: D64.2 (A), R65.2, U19.2
unnamed: D65.1 (K), R69.2
unnamed: D66.2 (A), U20.3
unnamed: D67.1 (K), R68.2, R69.1, R70.1
unnamed: D67.2 (A), R70.2, U20.2
unnamed: R6.2, R9.2, U8.4
unnamed: R10.1, U8.1
unnamed: R7.2, R12.2, U9.4
unnamed: R13.1, U9.1
unnamed: R8.2, R15.2, U10.4
unnamed: R16.1, U10.1
unnamed: R21.2, R24.2, U11.4
unnamed: R22.2, R27.2, U12.4
unnamed: R23.2, R30.2, U13.4
unnamed: R25.1, U11.1
unnamed: R28.1, U12.1
unnamed: R31.1, U13.1
unnamed: R36.2, R39.2, U14.4
unnamed: R37.2, R42.2, U15.4
unnamed: R38.2, R45.2, U16.4
unnamed: R40.1, U14.1
unnamed: R43.1, U15.1
unnamed: R46.1, U16.1
unnamed: R51.2, R54.2, U17.4
unnamed: R52.2, R57.2, U18.4
unnamed: R53.2, R60.2, U19.4
unnamed: R55.1, U17.1
unnamed: R58.1, U18.1
unnamed: R61.1, U19.1
unnamed: R66.2, R67.2, U20.4
unnamed: R68.1, U20.1
PA0: R60.1; also elsewhere on the board
PC0: R57.1; also elsewhere on the board
PC1: R15.1; also elsewhere on the board
PC2: R30.1; also elsewhere on the board
PC3: R45.1; also elsewhere on the board
PC13: R12.1; also elsewhere on the board
PC14: R27.1; also elsewhere on the board
PC15: R42.1; also elsewhere on the board
PE2: R9.1; also elsewhere on the board
PE3: R24.1; also elsewhere on the board
PE4: R39.1; also elsewhere on the board
PE5: R54.1; also elsewhere on the board
PE6: R67.1; also elsewhere on the board

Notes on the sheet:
Button M8
Button M7
Button STOP
Button M4
Button M3
Button M1
Button M10, M11, M12
SUM M3
Button M9 Revers
Button M5
Button M6
Button M9 Forvard
Button M2
